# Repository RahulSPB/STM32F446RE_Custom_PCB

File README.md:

---

# **STM32F446RE – Custom 4-Layer Development Board**

A custom-designed development board built around the **STM32F446RE** microcontroller, featuring stable power architecture, clean signal routing, multiple communication interfaces, and onboard peripherals for embedded systems development.

---

## **📌 Overview**

This project contains the complete hardware design for a **4-layer STM32F446RE development board**, built for firmware experimentation, sensor interfacing, and peripheral testing.
The board includes a solid ground plane, dedicated power plane, USB-C input, ESD protection, and connectors for UART, I²C, SPI, and SWD.

This repository includes:

* KiCad source files
* Schematic PDF
* Fabrication-ready Gerbers
* 3D renders
* Board overview and design notes

---

## **🧠 Key Features**

### **Microcontroller**

* STM32F446RE (Cortex-M4 @ 180 MHz)
* 512 KB Flash, 128 KB SRAM
* Full peripheral support: UART, SPI, I²C, ADC, Timers, DMA, GPIO

### **Clocking**

* High-Speed External Oscillator (HSE)
* Crystal placed with proper layout guidelines

### **Power System**

* USB-C power input
* AMS1111-3.3 LDO (VBUS → 3.3V)
* 5V rail available for USB
* Decoupling caps at every VDD pin
* Ferrite bead for noise filtering
* Polyfuse protection on VBUS
* Power LED indicator

### **Connectivity**

* **UART** – 4-pin header
* **I²C** – 4-pin header
* **SPI** – 10-pin header
* **SWD** – 4-pin debug/programming header
* Onboard **Si7021** temp/humidity sensor (I²C)
* LCD interface for 16×2 / 20×4 displays

---

## **🔧 PCB Stackup & Layout**

### **4-Layer Stackup**

* **Layer 1 (Top):** Signal
* **Layer 2:** Solid Ground Plane
* **Layer 3:** Power Plane (3.3V, 5V, VBUS islands)
* **Layer 4 (Bottom):** Signal

### **Routing Strategy**

* 0.3 mm trace width for general signals
* 0.5–0.6 mm for power & ground
* High-frequency noise minimized with ferrite bead
* Stitching vias across ground and power areas
* VBUS isolated to regulator & USB-C region

---

## **📁 Repository Structure**

```
stm32f446re_custom_pcb/
│
├── hardware/
│   ├── kicad_project/          # Main KiCad project files
│   ├── gerbers/                # Gerber files for fabrication
│   └── gerbers.zip             # Fabrication-ready ZIP
│   
├── documentation/
│   ├── schematic.pdf           # Full schematic
│   ├── pcb_3d_renders/         # 3D images of the PCB
│   └── board_overview.md       # Detailed design description
│
└── README.md                   # You are here
```

---

## **🛠 Tools Used**

* KiCad
* EasyEDA (optional early drafts)
* 3D Viewer & Gerber viewer
* USB-C reference design
* ST AN2606 / Datasheet guidelines

---

## **📐 Getting the Files Manufactured**

1. Download **gerbers.zip**
2. Upload to PCBWay / JLCPCB / OSHPark
3. Select **4-layer PCB**
4. Use default stackup unless otherwise stated
5. Confirm drill sizes & clearances

---

## **📸 Preview**

Screenshots of 3D renders:
(Add your `top_view.png`, `bottom_view.png`, etc. here)

```
documentation/pcb_3d_renders/
│── top_view.png
│── bottom_view.png
│── angled_view.png
```

---

## **📎 Notes**

* Boot0 is set via pull-down resistor (no switch)
* NRST uses a push-button reset switch
* Power, ground, and critical lines follow recommended ST layout guidelines
* Board is designed for HAL-based STM32 firmware development

---

## **📧 Contact**

If you want a contact section at the bottom:

```
Developer: Rahul Bagathi  
Email: Bagathi_ug_24@ei.nits.ac.in 
LinkedIn:https://www.linkedin.com/in/bagathi-rahul-b27411371 
GitHub: https://github.com/RahulSPB

```

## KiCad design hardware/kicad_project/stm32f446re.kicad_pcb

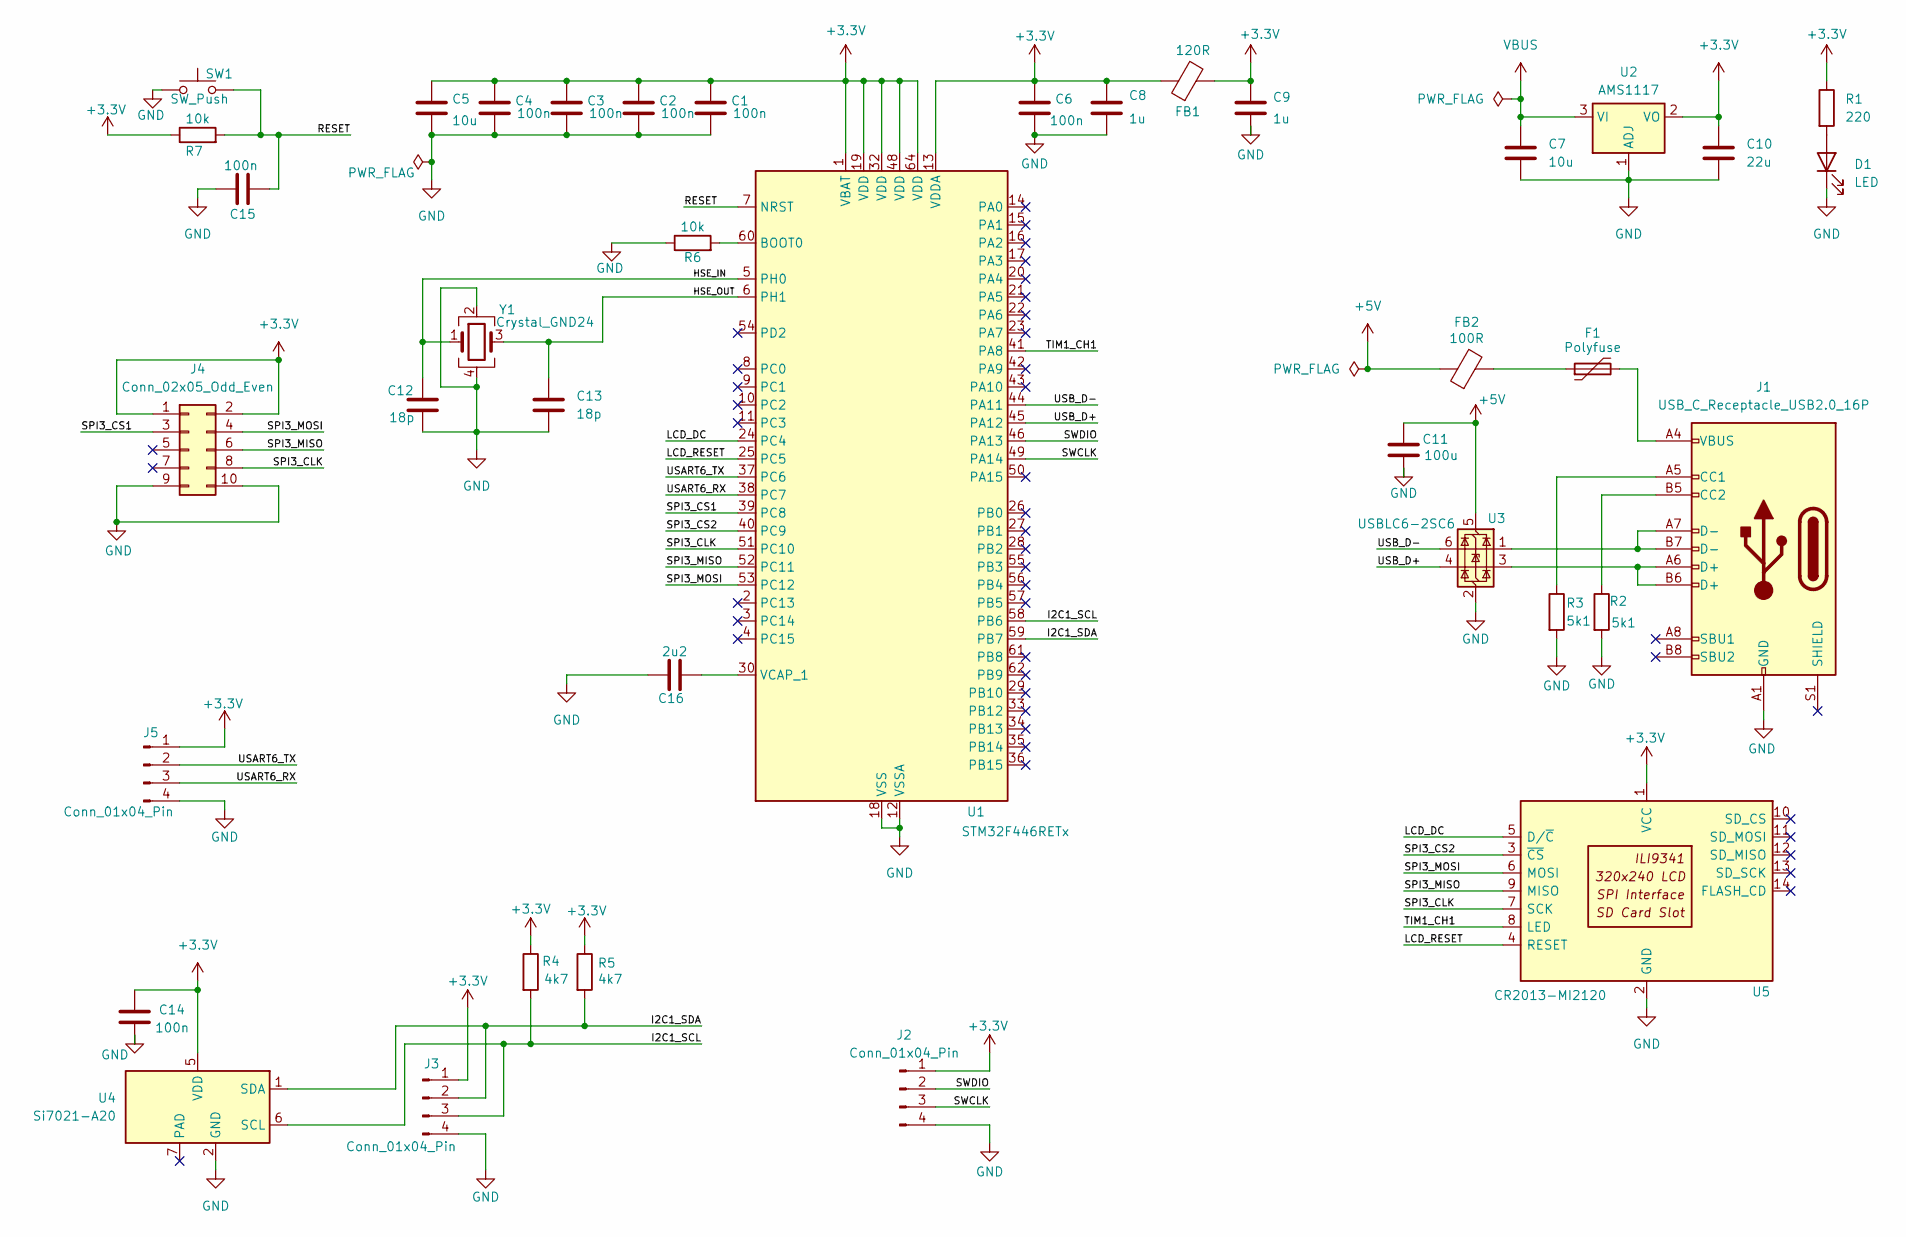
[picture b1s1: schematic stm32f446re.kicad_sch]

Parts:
C1, C2, C3, C4, C6, C14, C15: 100n; C_0402_1005Metric
C5, C7: 10u; C_0603_1608Metric
C8, C9: 1u; C_0603_1608Metric
C10: 22u; C_0805_2012Metric
C11: 100u; C_0805_2012Metric
C12, C13: 18p; C_0402_1005Metric
C16: 2u2; C_0603_1608Metric
D1: LED; LED_0603_1608Metric
F1: Polyfuse; Fuse_0402_1005Metric
FB1: 120R; L_0603_1608Metric
FB2: 100R; L_0603_1608Metric
J1: USB_C_Receptacle_USB2.0_16P; USB_C_Receptacle_GCT_USB4105-xx-A_16P_TopMnt_Horizontal
J2, J3, J5: Conn_01x04_Pin; PinHeader_1x04_P2.54mm_Vertical
J4: Conn_02x05_Odd_Even; PinHeader_2x05_P2.54mm_Vertical
R1: 220; R_0402_1005Metric
R2, R3: 5k1; R_0402_1005Metric
R4, R5: 4k7; R_0402_1005Metric
R6, R7: 10k; R_0402_1005Metric
SW1: SW_Push; SW_Push_SPST_NO_Alps_SKRK
U1: STM32F446RETx; LQFP-64_10x10mm_P0.5mm
U2: AMS1117; SOT-223-3_TabPin2
U3: USBLC6-2SC6; SOT-23-6
U4: Si7021-A20; DFN-6-1EP_3x3mm_P1mm_EP1.5x2.4mm
U5: CR2013-MI2120
Y1: Crystal_GND24; Crystal_SMD_3225-4Pin_3.2x2.5mm

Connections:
+3.3V: C1.1, C2.1, C3.1, C4.1, C5.1, C6.1, C8.1, C9.1, C10.1, C14.1, FB1.1, FB1.2, J2.1, J3.1, J4.1, J4.2, J5.1, R1.1, R4.1, R5.1, R7.1, U1.1 (VBAT), U1.13 (VDDA), U1.19 (VDD), U1.32 (VDD), U1.48 (VDD), U1.64 (VDD), U2.2 (VO), U4.5 (VDD), U5.1 (VCC)
+5V: C11.1, FB2.1, U3.5 (VBUS)
/HSE_IN: C12.1, U1.5 (PH0), Y1.1
/HSE_OUT: C13.1, U1.6 (PH1), Y1.3
/I2C1_SCL: J3.3, R4.2, U1.58 (PB6), U4.6 (SCL)
/I2C1_SDA: J3.2, R5.2, U1.59 (PB7), U4.1 (SDA)
/LCD_DC: U1.24 (PC4), U5.5 (D/~C)
/LCD_RESET: U1.25 (PC5), U5.4 (RESET)
/RESET: C15.2, R7.2, SW1.2, U1.7 (NRST)
/SPI3_CLK: J4.8, U1.51 (PC10), U5.7 (SCK)
/SPI3_CS1: J4.3, U1.39 (PC8)
/SPI3_CS2: U1.40 (PC9), U5.3 (~CS)
/SPI3_MISO: J4.6, U1.52 (PC11), U5.9 (MISO)
/SPI3_MOSI: J4.4, U1.53 (PC12), U5.6 (MOSI)
/SWCLK: J2.3, U1.49 (PA14)
/SWDIO: J2.2, U1.46 (PA13)
/TIM1_CH1: U1.41 (PA8), U5.8 (LED)
/USART6_RX: J5.3, U1.38 (PC7)
/USART6_TX: J5.2, U1.37 (PC6)
/USB_D+: U1.45 (PA12), U3.4 (I/O2)
/USB_D-: U1.44 (PA11), U3.6 (I/O1)
GND: C1.2, C2.2, C3.2, C4.2, C5.2, C6.2, C7.2, C8.2, C9.2, C10.2, C11.2, C12.2, C13.2, C14.2, C15.1, C16.1, D1.1 (K), J1.A1 (GND), J1.A12 (GND), J1.B1 (GND), J1.B12 (GND), J2.4, J3.4, J4.9, J4.10, J5.4, R2.2, R3.2, R6.1, SW1.1, U1.12 (VSSA), U1.18 (VSS), U1.31 (VSS), U1.47 (VSS), U1.63 (VSS), U2.1 (ADJ), U3.2 (GND), U4.2 (GND), U5.2 (GND), Y1.2, Y1.4
unnamed: D1.2 (A), R1.2
unnamed: F1.1, FB2.2
unnamed: F1.2, J1.A4 (VBUS), J1.A9 (VBUS), J1.B4 (VBUS), J1.B9 (VBUS)
unnamed: J1.A5 (CC1), R3.1
unnamed: J1.B5 (CC2), R2.1
unnamed: J1.A6 (D+), J1.B6 (D+), U3.3 (I/O2)
unnamed: J1.A7 (D-), J1.B7 (D-), U3.1 (I/O1)
unnamed: R6.2, U1.60 (BOOT0)
unnamed: C16.2, U1.30 (VCAP_1)
VBUS: C7.1, U2.3 (VI)

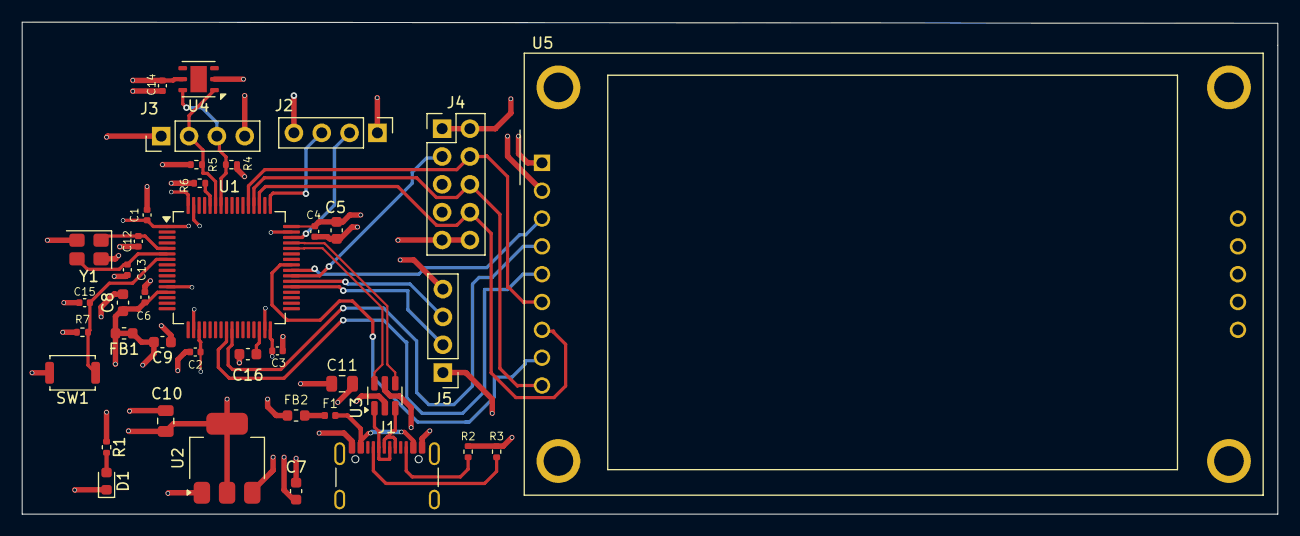
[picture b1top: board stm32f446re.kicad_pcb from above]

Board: 4 copper layers, 114.6 x 44.9 mm, 39 parts (0 on the bottom side), 32 nets.

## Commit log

2025-11-14 Added hardware and documentation folders
